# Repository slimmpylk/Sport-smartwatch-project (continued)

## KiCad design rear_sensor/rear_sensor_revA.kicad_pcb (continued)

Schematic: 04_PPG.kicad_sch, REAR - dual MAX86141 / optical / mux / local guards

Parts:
C403, C404, C405, C406, C407, C408, C4102, C4202: 100nF; C_0402_1005Metric
C4101, C4201: 22uF; C_0402_1005Metric
C4103, C4203: 1.0uF; C_0402_1005Metric
C4104, C4204: 10uF; C_0402_1005Metric
D401, D402, D403, D404: SFH7018A Q65113A6157; OSRAM_SFH7018A_2.4x2.4mm
D405, D406, D407: SFH4053B Q65115A1586; OSRAM_SFH4053B_1.0x0.5mm
D413, D414, D423, D424: SFH2703H Q65115A2199; OSRAM_SFH2703_3.2x2.0mm
NT401: PPG1_PD_GND_TIE; NetTie-2_SMD_Pad0.5mm
NT402: PPG2_PD_GND_TIE; NetTie-2_SMD_Pad0.5mm
R401, R402, R405: 100k; R_0402_1005Metric
R403, R404: 47k; R_0402_1005Metric
R408, R409: 10k; R_0402_1005Metric
U12, U13: MAX86141ENP+T; 21-100134_N201A2-1_MXM
U402, U403, U404, U405, U406, U407: TS5A12301E; Texas_DSBGA-6_0.76x1.16mm_Layout2x3_P0.4mm

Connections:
/Optical/PPG1_LED1_GREEN_K: D401.1 (K_GREEN_1), D401.7 (K_GREEN_2), D401.8 (K_GREEN_3), U402.A1 (NO)
/Optical/PPG1_LED2_RED_K: D401.5 (K_RED), U403.A1 (NO)
/Optical/PPG1_LED3_IR850_K: D405.2 (CATHODE), U404.A1 (NO)
/Optical/PPG1_LED4_GREEN_K: D403.1 (K_GREEN_1), D403.7 (K_GREEN_2), D403.8 (K_GREEN_3), U402.C1 (NC)
/Optical/PPG1_LED5_RED_K: D403.5 (K_RED), U403.C1 (NC)
/Optical/PPG1_LED6_IR850_K: D406.2 (CATHODE), U404.C1 (NC)
/Optical/PPG1_LED_GREEN_DRV: U12.D1 (LED1_DRV), U402.B2 (COM)
/Optical/PPG1_LED_IR_DRV: U12.B1 (LED3_DRV), U404.B2 (COM)
/Optical/PPG1_LED_MUX_SEL: R408.2, U12.B4 (GPIO2), U402.A2 (IN), U403.A2 (IN), U404.A2 (IN)
/Optical/PPG1_LED_RED_DRV: U12.C1 (LED2_DRV), U403.B2 (COM)
/Optical/PPG1_PD1_IN: D424.1 (CATHODE), U12.D5 (PD1_IN)
/Optical/PPG1_PD2_IN: D414.1 (CATHODE), U12.D4 (PD2_IN)
/Optical/PPG1_PD_GND: D414.2 (ANODE), D424.2 (ANODE), NT401.1 (A), U12.C5 (PD_GND)
/Optical/PPG1_VREF: C4103.1, U12.B5 (VREF)
/Optical/PPG2_LED1_GREEN_K: D402.1 (K_GREEN_1), D402.7 (K_GREEN_2), D402.8 (K_GREEN_3), U405.A1 (NO)
/Optical/PPG2_LED2_RED_K: D402.5 (K_RED), U406.A1 (NO)
/Optical/PPG2_LED3_IR850_K: D407.2 (CATHODE), U407.A1 (NO)
/Optical/PPG2_LED4_GREEN_K: D404.1 (K_GREEN_1), D404.7 (K_GREEN_2), D404.8 (K_GREEN_3), U405.C1 (NC)
/Optical/PPG2_LED5_RED_K: D404.5 (K_RED), U406.C1 (NC)
/Optical/PPG2_LED6_IR940_K: D402.3 (K_IR), U407.C1 (NC)
/Optical/PPG2_LED_GREEN_DRV: U13.D1 (LED1_DRV), U405.B2 (COM)
/Optical/PPG2_LED_IR_DRV: U13.B1 (LED3_DRV), U407.B2 (COM)
/Optical/PPG2_LED_MUX_SEL: R409.2, U13.B4 (GPIO2), U405.A2 (IN), U406.A2 (IN), U407.A2 (IN)
/Optical/PPG2_LED_RED_DRV: U13.C1 (LED2_DRV), U406.B2 (COM)
/Optical/PPG2_PD1_IN: D423.1 (CATHODE), U13.D5 (PD1_IN)
/Optical/PPG2_PD2_IN: D413.1 (CATHODE), U13.D4 (PD2_IN)
/Optical/PPG2_PD_GND: D413.2 (ANODE), D423.2 (ANODE), NT402.1 (A), U13.C5 (PD_GND)
/Optical/PPG2_VREF: C4203.1, U13.B5 (VREF)
GND: C403.2, C404.2, C405.2, C406.2, C407.2, C408.2, C4101.2, C4102.2, C4103.2, C4104.2, C4201.2, C4202.2, C4203.2, C4204.2, NT401.2 (B), NT402.2 (B), U12.C3 (GND_DIG), U12.C4 (GND_ANA), U12.D3 (PGND), U13.C3 (GND_DIG), U13.C4 (GND_ANA), U13.D3 (PGND), U402.B1 (GND), U403.B1 (GND), U404.B1 (GND), U405.B1 (GND), U406.B1 (GND), U407.B1 (GND); also elsewhere on the board
PPG1_CS_N: R401.2, U12.A5 (CSB)
PPG1_INT_N: R403.2, U12.B2 (*INT)
PPG2_CS_N: R402.2, U13.A5 (CSB)
PPG2_INT_N: R404.2, U13.B2 (*INT)
PPG_SAMPLE_SYNC: R405.2, U12.B3 (GPIO1), U13.B3 (GPIO1)
PPG_SPI_MISO: U12.A3 (SDO), U13.A3 (SDO)
PPG_SPI_MOSI: U12.A4 (SDI), U13.A4 (SDI)
PPG_SPI_SCLK: U12.A2 (SCLK), U13.A2 (SCLK)
PPG_VLED: C403.1, C404.1, C405.1, C406.1, C407.1, C408.1, C4104.1, C4204.1, D401.2 (A_RED_IR_1), D401.4 (A_RED_IR_2), D401.6 (A_GREEN), D402.2 (A_RED_IR_1), D402.4 (A_RED_IR_2), D402.6 (A_GREEN), D403.2 (A_RED_IR_1), D403.4 (A_RED_IR_2), D403.6 (A_GREEN), D404.2 (A_RED_IR_1), D404.4 (A_RED_IR_2), D404.6 (A_GREEN), D405.1 (ANODE), D406.1 (ANODE), D407.1 (ANODE), U12.A1 (VLED), U13.A1 (VLED), U402.C2 (VCC), U403.C2 (VCC), U404.C2 (VCC), U405.C2 (VCC), U406.C2 (VCC), U407.C2 (VCC)
VOUT1_1V8: C4101.1, C4102.1, C4201.1, C4202.1, R401.1, R402.1, R403.1, R404.1, R405.1, R408.1, R409.1, U12.C2 (VDD_DIG), U12.D2 (VDD_ANA), U13.C2 (VDD_DIG), U13.D2 (VDD_ANA); also elsewhere on the board

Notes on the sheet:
Board ownership and interfaces: design/interfaces/main_rear_interface.md
One current path per AFE per exposure. Red <=31mA; green/IR <=62mA initial firmware limits.
PD_GND -> NT401/NT402 -> local system GND. Rebuild physical guards on future REAR layout.

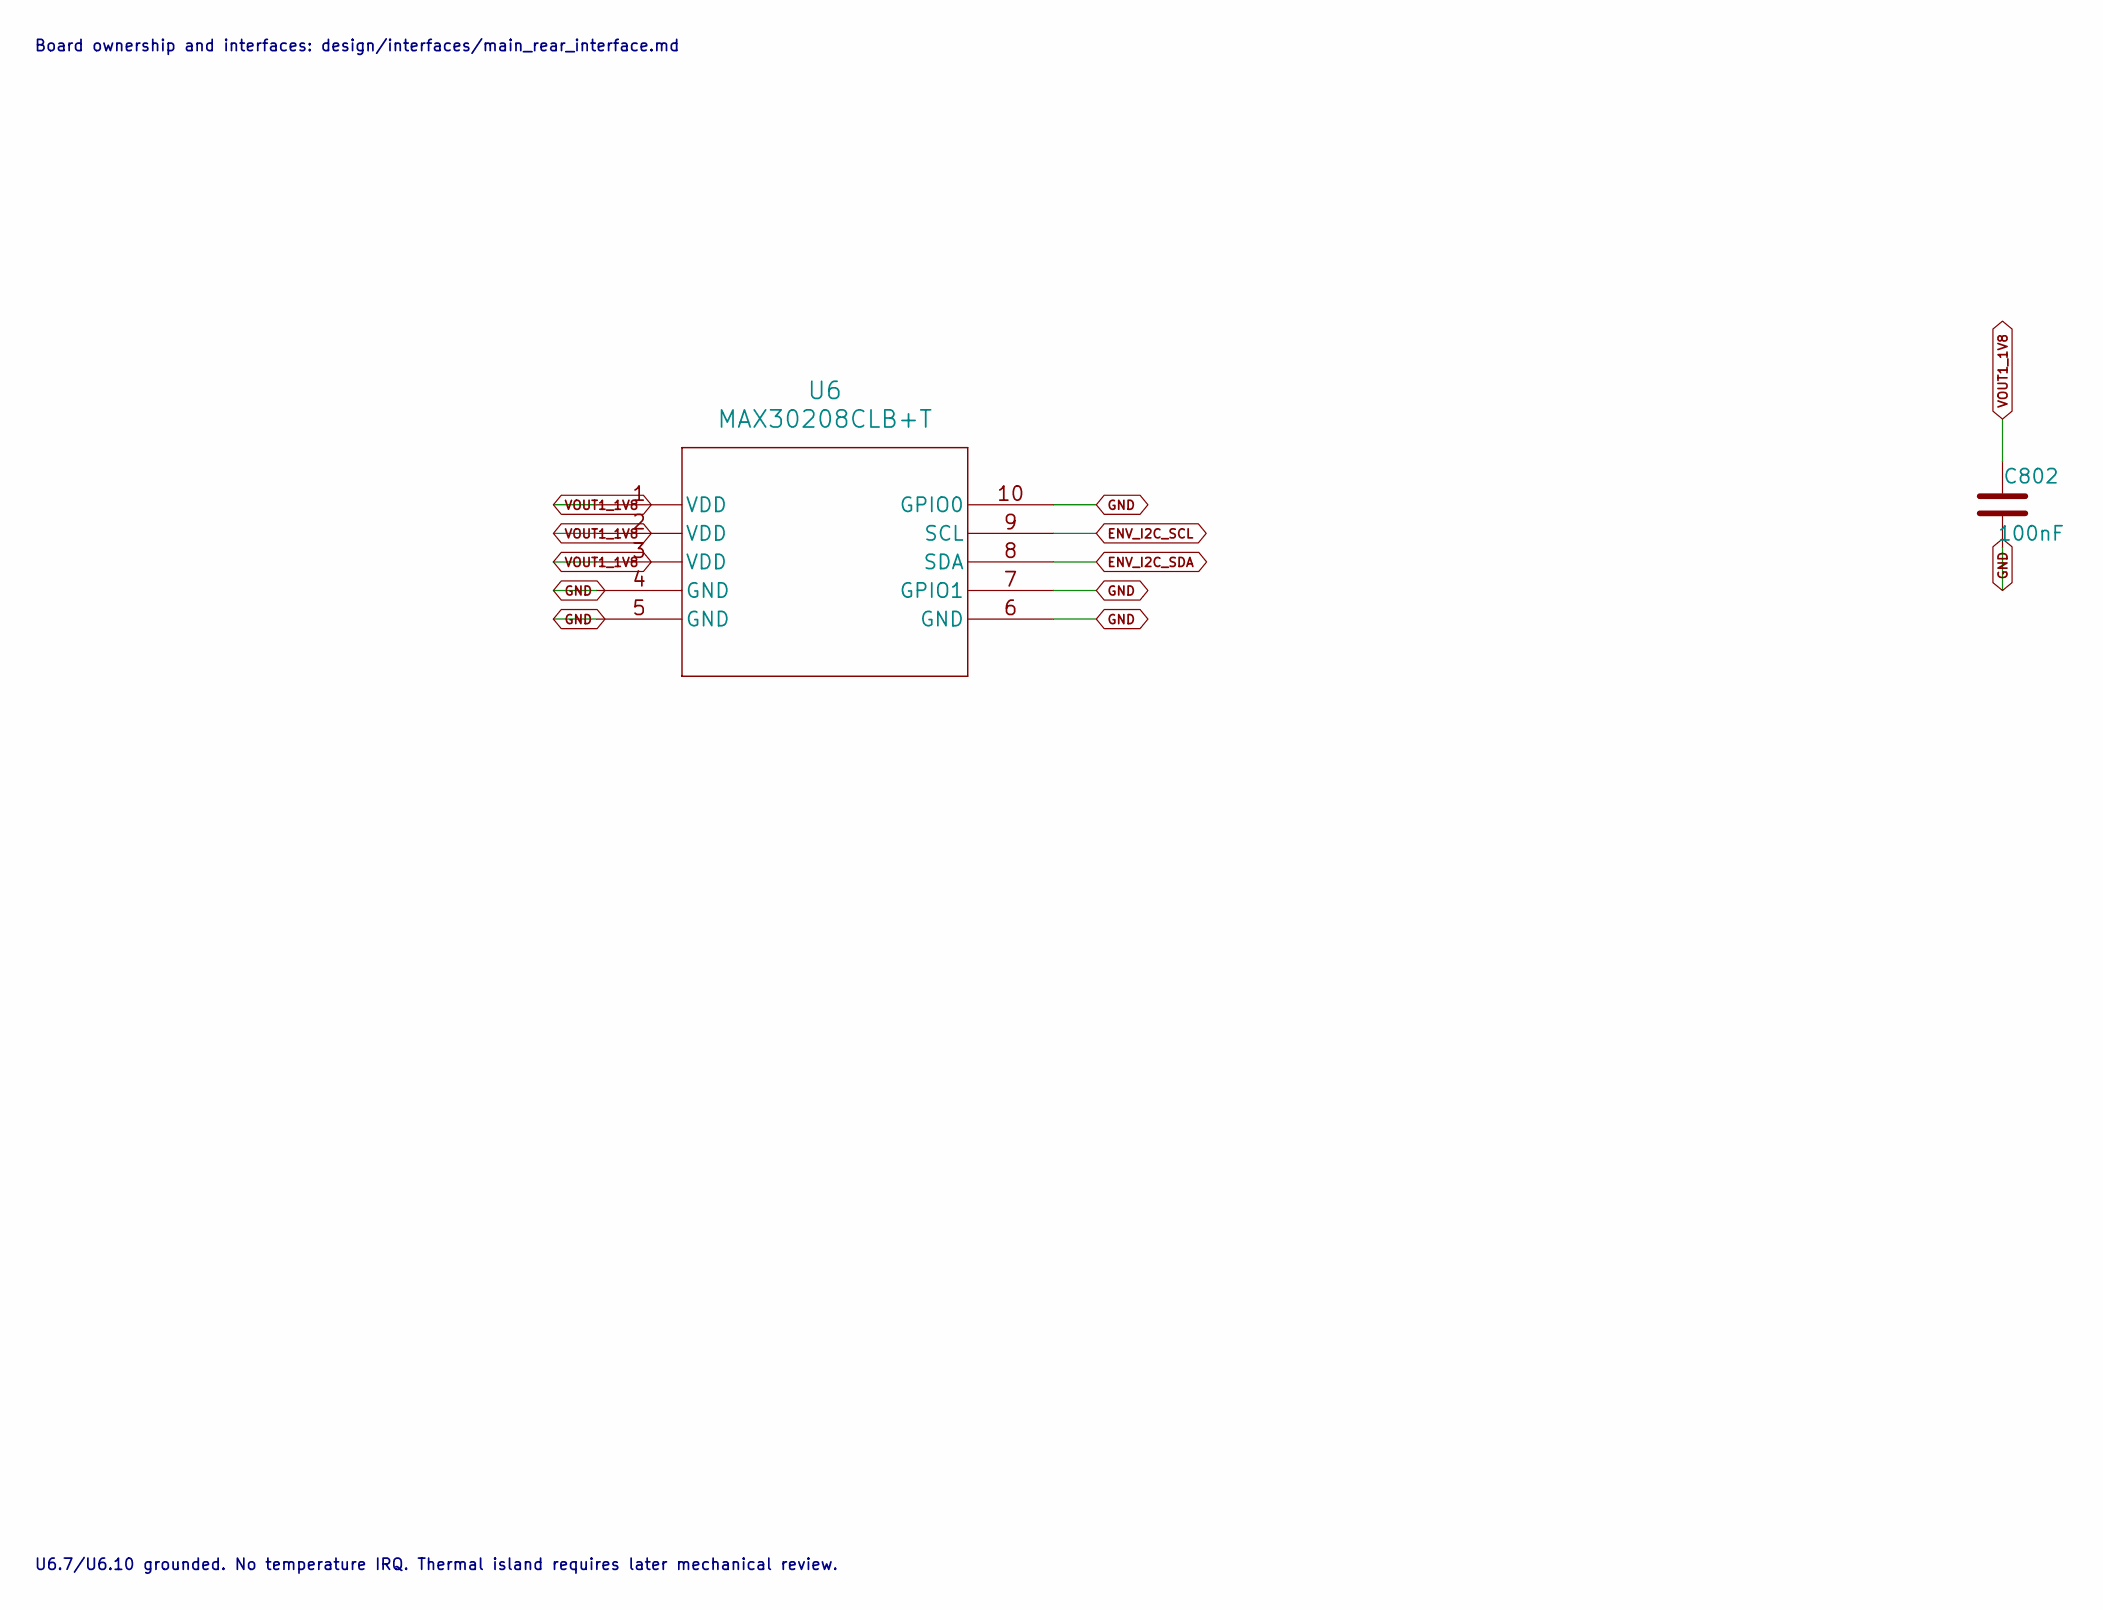
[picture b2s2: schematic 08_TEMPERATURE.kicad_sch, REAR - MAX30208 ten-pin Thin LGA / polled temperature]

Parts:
C802: 100nF; C_0402_1005Metric
U6: MAX30208CLB+T; 21-100265_MXM

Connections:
ENV_I2C_SCL: U6.9 (SCL)
ENV_I2C_SDA: U6.8 (SDA)
GND: C802.2, U6.4 (GND), U6.5 (GND), U6.6 (GND), U6.7 (GPIO1), U6.10 (GPIO0); also elsewhere on the board
VOUT1_1V8: C802.1, U6.1 (VDD), U6.2 (VDD), U6.3 (VDD); also elsewhere on the board

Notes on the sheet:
Board ownership and interfaces: design/interfaces/main_rear_interface.md
U6.7/U6.10 grounded. No temperature IRQ. Thermal island requires later mechanical review.

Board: 2 copper layers, 44 parts (0 on the bottom side), 39 nets, no tracks yet.

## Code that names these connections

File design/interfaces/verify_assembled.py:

#!/usr/bin/env python3
"""Audit native per-root XML through the tracked abstract harness contract.

Usage: python3 design/interfaces/verify_assembled.py MAIN.xml REAR.xml OUTPUT.json
No KiCad/akcli Python packages required. Exits nonzero on any failed assertion.
"""
import csv, hashlib, json, sys, xml.etree.ElementTree as ET
from collections import Counter, defaultdict
from pathlib import Path
BASE=Path(__file__).resolve().parent
ROOT=BASE.parent.parent

def load(path):
    r=ET.parse(path).getroot()
    cs=r.findall('components/comp')
    refs=[c.get('ref') for c in cs]
    assert len(refs)==len(set(refs)), f'Duplicate references: {path}'
    nets={n.get('name'): {(p.get('ref'),p.get('pin')) for p in n.findall('node')} for n in r.findall('nets/net')}
    pin={p:n for n,ps in nets.items() for p in ps}
    return {c.get('ref'):c for c in cs}, nets, pin

def audit(main_path,rear_path):
    source=json.loads((BASE/'source_pin_membership.json').read_text())
    checkpoint=json.loads((BASE/'source_checkpoint.json').read_text())
    contract=json.loads((BASE/'main_rear_interface.json').read_text())
    charger=json.loads((BASE/'charger_harness.json').read_text())
    main,mnets,mpins=load(main_path);rear,rnets,rpins=load(rear_path)
    assert not set(main)&set(rear), 'References reused across roots'
    assert rear['C1501'].find("property[@name='dnp']") is not None, 'C1501 must remain DNP'
    expected_rear={r for r,o in checkpoint['ownership'].items() if o=='REAR'}
    assert len(expected_rear)==44 and expected_rear<=set(rear)
    assert not expected_rear&set(main)
    assert set(source)-expected_rear<=set(main)
    for ref,c in main.items():
        assert c.find("property[@name='Board']").get("value")=='MAIN', (ref,'MAIN Board field missing')
    for ref,c in rear.items():
        assert c.find("property[@name='Board']").get("value")=='REAR', (ref,'REAR Board field missing')
    # Union only actual connector-connected net nodes, not equal text between roots.
    parent={('MAIN',n):('MAIN',n) for n in mnets}|{('REAR',n):('REAR',n) for n in rnets}
    def find(n):
        while parent[n]!=n:
            parent[n]=parent[parent[n]];n=parent[n]
        return n
    def join(a,b):parent[find(b)]=find(a)
    continuity=[]
    for row in contract['positions']:
        p=str(row['position']);m=mpins[('J1501',row['main_pin'])];r=rpins[('J1502',row['rear_pin'])]
        assert m.split('/')[-1]==r.split('/')[-1]==row['net'],(p,m,r,row['net'])
        join(('MAIN',m),('REAR',r))
        continuity.append({'position':int(p),'net':row['net'],'main_net':m,'rear_net':r,'pass':True})
    counts=Counter(x['net'] for x in continuity)
    assert len(counts)==13 and counts['GND']==10 and counts['PPG_VLED']==3 and counts['VOUT1_1V8']==1
    assert sum(v for n,v in counts.items() if n not in ['GND','PPG_VLED','VOUT1_1V8'])==10
    groups=defaultdict(set)
    for board,nets in [('MAIN',mnets),('REAR',rnets)]:
        for net,pins in nets.items():
            groups[find((board,net))].update(p for p in pins if p[0] in source and p[0]!='J202')
    assembled={frozenset(s) for s in groups.values() if s}
    original=defaultdict(set)
    for ref,ps in source.items():
        if ref=='J202':continue  # intentional raw-to-protected charger ECO
        for pin,net in ps.items():original[net].add((ref,pin))
    expected={frozenset(s) for s in original.values() if s}
    assert assembled==expected, {'missing_original_groups':[sorted(s) for s in expected-assembled],'unexpected_groups':[sorted(s) for s in assembled-expected]}
    # Explicit detector and local shield proofs, in addition to the full partition comparison.
    detector=[]
    for d,u,p in [('D424','U12','D5'),('D414','U12','D4'),('D423','U13','D5'),('D413','U13','D4')]:
        members=rnets[rpins[(u,p)]]
        assert any(ref==d for ref,pin in members), (d,u,p)
        detector.append({'detector':d,'afe':u,'pin':p,'members':sorted(members),'pass':True})
    for nt,n in [('NT401','PPG1_PD_GND'),('NT402','PPG2_PD_GND')]:
        assert rpins[(nt,'1')].split('/')[-1]==n and rpins[(nt,'2')].split('/')[-1]=='GND'
    assert {r for r in rear if r in ['R801','R802']}==set()
    assert mpins[('J201','1')]=='GND' and mpins[('J201','2')].endswith('BAT_NTC') and mpins[('J201','3')].endswith('VBAT')
    assert mpins[('C206','1')].endswith('VBAT') and mpins[('C206','2')]=='GND'
    assert mpins[('U201','21')]==mpins[('C201','1')]==mpins[('U1201','2')]==mpins[('D1201','1')]
    assert mpins[('J202','1')]==mpins[('U1201','1')]=='CHG_RAW_5V'
    assert mpins[('U1201','1')]!=mpins[('U1201','2')], 'Protection bypassed'
    assert mpins[('J202','2')]=='GND'
    for row in charger['external_contacts']:
        assert mpins[(row['main_ref'],row['main_pin'])]==row['net']
    for p in ['7','10']:assert rpins[('U6',p)]=='GND'
    # All transferred source symbol UUIDs and pin UUIDs remain intact.
    src,_,_=load(BASE/'source_netlist.xml')
    for ref in source:
        if ref=='J202':continue
        new=(rear if ref in expected_rear else main)[ref]
        assert new.findtext('tstamps')==src[ref].findtext('tstamps'), (ref,'symbol UUID changed')
        assert new.findtext('value')==src[ref].findtext('value'),(ref,'value changed')
        assert new.findtext('footprint')==src[ref].findtext('footprint'),(ref,'footprint changed')
    # Tracked library definitions remain byte-identical.
    protected=[]
    for file,sha in checkpoint['hashes'].items():
        if file.endswith(('.kicad_sym','.kicad_mod')) or file=='fp-lib-table':
            assert hashlib.sha256((ROOT/file).read_bytes()).hexdigest()==sha, file+' protected file modified'
            protected.append(file)
    return {'status':'PASS','source_commit':checkpoint['commit'],'counts':{'MAIN':{'components':len(main),'nets':len(mnets)},'REAR':{'components':len(rear),'nets':len(rnets)},'HARNESS':{'contacts':4,'logical_nets':2,'bom_lines':len(charger['population'])}},'transferred_existing_components':44,'boundary_logical_nets':13,'continuity':continuity,'detectors':detector,'all_original_pin_partitions_preserved_except_deliberate_J202_protection_ECO':True,'all_LED_mux_VREF_PD_GND_unused_cathode_memberships_preserved':True,'source_components_checked':len(source)-1,'protected_hashes_verified':protected,'charger_protection':'provisional mandatory block, no selected IC / hardware immunity claim'}

def bom(xml_path,board):
    cs,_,_=load(xml_path)
    with (BASE/'validation'/f'{board.lower()}_bom.csv').open('w') as f:
        w=csv.writer(f, lineterminator="\n");w.writerow(['Reference','Value','Footprint','Board','DNP','SelectionStatus'])
        for ref,c in sorted(cs.items()):
            w.writerow([ref,c.findtext('value'),c.findtext('footprint'),board,c.find('property[@name="dnp"]') is not None,(c.find('property[@name="SelectionStatus"]').get("value") if c.find('property[@name="SelectionStatus"]') is not None else None) or 'BASELINE'])

if __name__=='__main__':
    assert len(sys.argv)==4, __doc__
    result=audit(sys.argv[1],sys.argv[2]);Path(sys.argv[3]).write_text(json.dumps(result,indent=2)+'\n')
    for file,board in [(sys.argv[1],'MAIN'),(sys.argv[2],'REAR')]:bom(file,board)
    print(json.dumps({'status':result['status'],'counts':result['counts'],'transferred':44,'boundary_nets':13,'original_pin_partitions':'PASS'}))
